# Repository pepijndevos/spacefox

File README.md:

# SpaceFox

A 6DOF DIY HID. A what? A 6 degrees of freedom, do it yourself, human interface device. In other words, a 3D mouse, or an open hardware SpaceNavigator. You know, one of these thingies CAD designers use to zoom around.

All the existing DIY designs out there I could find are not actually 6DOF. Some are literally a knob on a joystick. So I set out to make a better one.

This one is based on a stewart platform made from potentiometers. It was designed so that any idiot with access to a 3D printer can build one. You might even get away with some careful jigsawing!

## Other true 6DOF projects

Since doing this project I've become aware of a few other people making true 6DOF DIY spacemice that may actually be worth your time.

* [Space Mushroom](https://www.instructables.com/Space-Mushroom-Full-6-DOFs-Controller-for-CAD-Appl/)
* [Haptick](https://blog.ioces.com/matt/posts/haptick-part-two/)

## Gallery

Watch the Youtube video:

Close-up of the spring-loaded potentiometers:

CAD model of one of the arms:

CAD model of the knob:

CAD model of the base

## Bill of Materials

* 3x arm-Body + arm2-Body, 3D printed.
* 1x top-Body, 3D printed.
* 1x base, cut from 4 layers of 4mm triplex.
* 1x PCB [Aisler](https://aisler.net/p/TOQVENVP)
* 6x potentiometer, 6mm flatted shaft [Farnell](https://nl.farnell.com/tt-electronics-bi-technologies/p120k-f20br5k/potentiometer-rotary-5k-20mm-20/dp/2771751)
* 1x Arduino Pro Micro [Sparkfun](https://www.sparkfun.com/products/12640) [AliExpress](https://www.aliexpress.com/item/32768308647.html)
* 12x ball joint rod ends, 2mm, half pad [AliExpress](https://www.aliexpress.com/item/1005003423670988.html)
* 6x torsion spring, 1mm diameter, 3mm length, 90 degrees, 8.5mm outer diameter [AliExpress](https://www.aliexpress.com/item/1005003823259348.html)
* 6x threaded rod, 2mm, 20mm length [AliExpress](https://nl.aliexpress.com/item/1005002781646885.html)
* 9x Cherry MX compatible switches [AliExpress](https://nl.aliexpress.com/item/1005004285423123.html)
* 9x keycaps [AliExpress](https://nl.aliexpress.com/item/1005003302173904.html)
* 2mm & 3mm nuts and bolts
* 0.1" male & female headers

## Assembly instructions

1. Put the springs on the potentionmeters and snap them onto the PCB. Solder. Cut the ends short below the PCB.
2. Push the male and female headers together and insert them between the Arduino and PCB. Solder. (This way you ensure they end up straight)
3. Slide the arms halfway onto the potentionmeters facing 45 degree outwards. Apply a drop of hot glue to the slot for the spring and push them all the way in. Apply hot glue to secure the arm to the shaft.
4. Screw the rod ends onto the push rods and secure the rod ends to the arm with nuts and bolts.
5. Secure the knob to the rod ends with bolts.
7. Cut 4 sheets of the base plate (the middle sheet twice)
8. Insert Cherry MX switches in the top plate
9. Wire switches to the header on the PCB
11. Bolt the base plates together
10. Bolt the PCB onto the base plate
6. Upload the Arduino code.
8. Install [spacenavd](https://github.com/FreeSpacenav/spacenavd) and add `device-id = 1b4f:9206` to `/etc/spnavrc`.

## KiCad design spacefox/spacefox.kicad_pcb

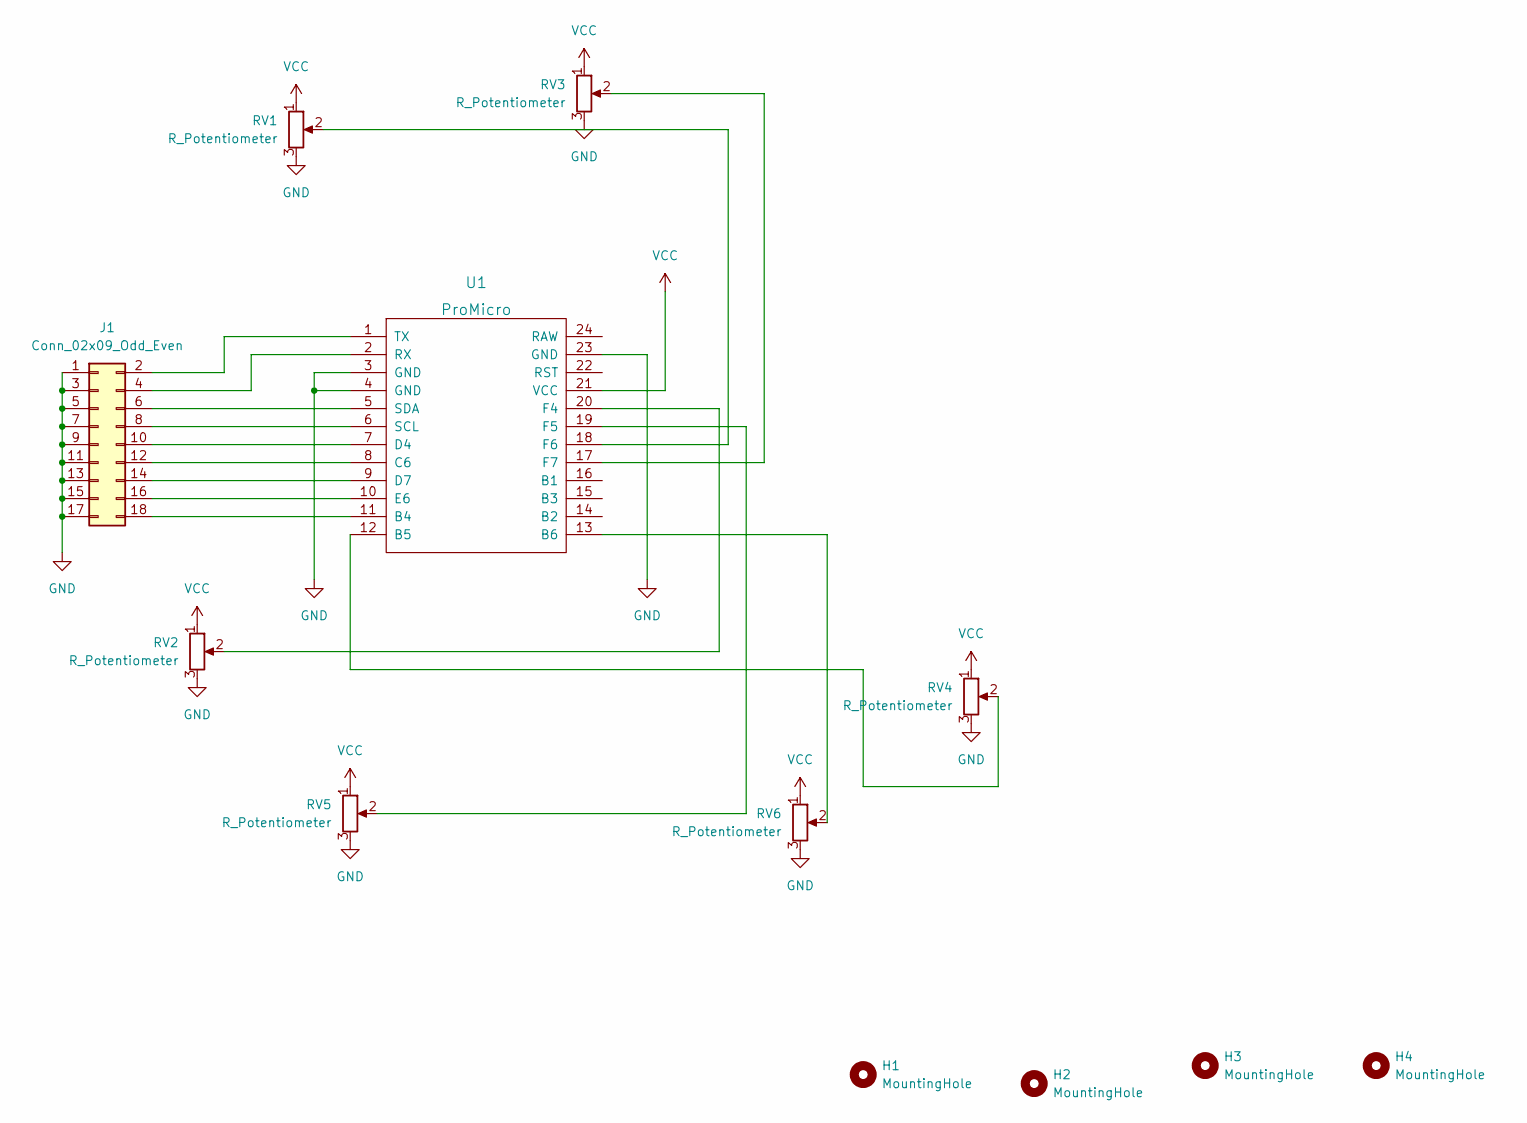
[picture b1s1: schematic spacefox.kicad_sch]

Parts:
H1, H2, H3, H4: MountingHole; MountingHole_3.2mm_M3
J1: Conn_02x09_Odd_Even; PinHeader_2x09_P2.54mm_Vertical
RV1, RV2, RV3, RV4, RV5, RV6: R_Potentiometer; TT_P120
U1: ProMicro

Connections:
GND: J1.1, J1.3, J1.5, J1.7, J1.9, J1.11, J1.13, J1.15, J1.17, RV1.3, RV2.3, RV3.3, RV4.3, RV5.3, RV6.3, U1.3 (GND), U1.4 (GND), U1.23 (GND)
unnamed: RV1.2, U1.18 (F6)
unnamed: RV2.2, U1.20 (F4)
unnamed: RV3.2, U1.17 (F7)
unnamed: RV4.2, U1.12 (B5)
unnamed: RV5.2, U1.19 (F5)
unnamed: RV6.2, U1.13 (B6)
unnamed: J1.2, U1.1 (TX)
unnamed: J1.4, U1.2 (RX)
unnamed: J1.6, U1.5 (SDA)
unnamed: J1.8, U1.6 (SCL)
unnamed: J1.10, U1.7 (D4)
unnamed: J1.12, U1.8 (C6)
unnamed: J1.14, U1.9 (D7)
unnamed: J1.16, U1.10 (E6)
unnamed: J1.18, U1.11 (B4)
VCC: RV1.1, RV2.1, RV3.1, RV4.1, RV5.1, RV6.1, U1.21 (VCC)

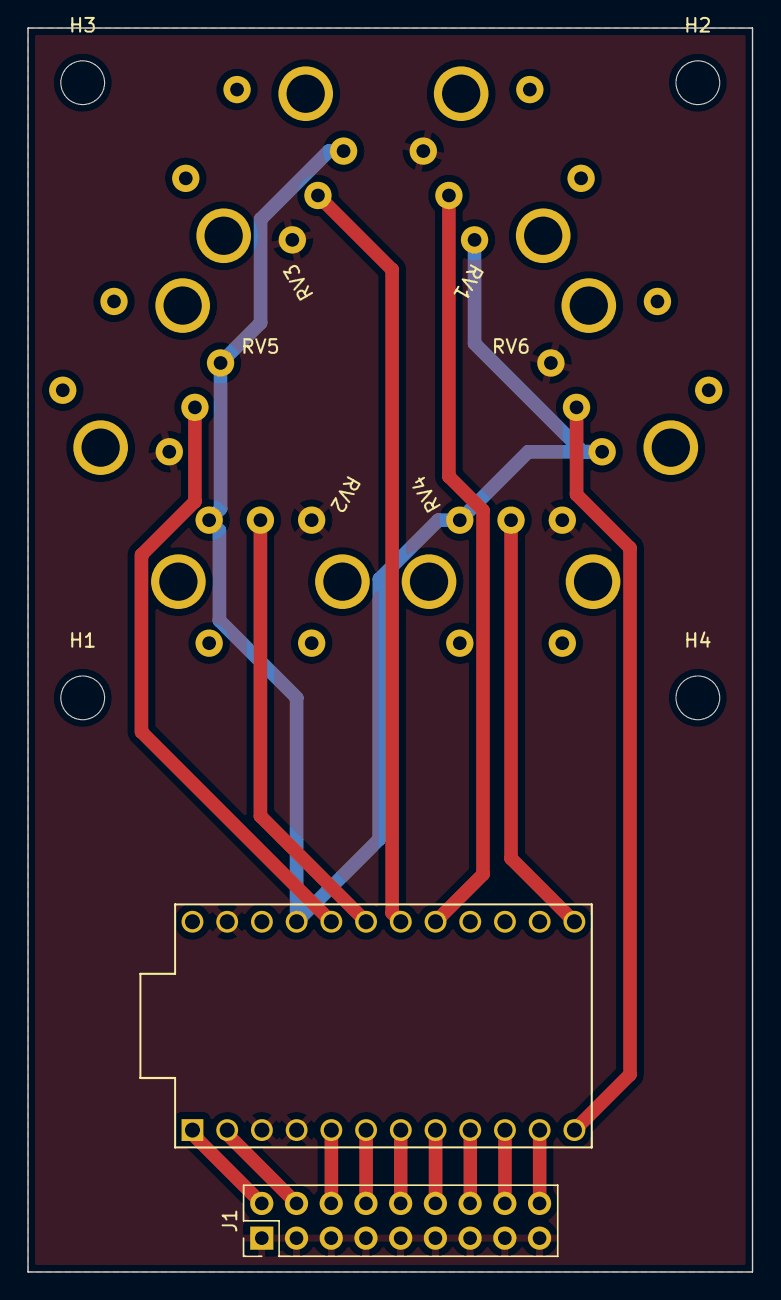
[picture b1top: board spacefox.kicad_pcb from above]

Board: 2 copper layers, 53.0 x 91.0 mm, 12 parts (0 on the bottom side), 17 nets.

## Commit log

2022-11-03 remove backups
2022-11-03 update arm for springs
2022-11-03 updated arms
2022-11-05 add arduino code and knob
2022-11-06 add exported body
2022-11-06 flip axis to match spacenavd
2022-11-10 WIP V2 PCB
2022-12-11 update top knob
2022-12-21 tweak dimensions
2023-01-17 add base plate
2023-01-21 update arduino code for v2 PCB
2023-01-22 update base
